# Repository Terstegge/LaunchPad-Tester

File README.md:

# LaunchPad-Tester
This is a small TI-LaunchPad compatible boosterpack board,
which can be used for testing all GPIO pins on a TI LaunchPad.

_Background:_ When using TI LaunchPads for educational purposes,
some of the IO-pins might be destroyed by students. So I needed
a simple way to test all IO pins of such boards before using
the boards during the next semester.

I had some spare [CY8C9540A](http://www.cypress.com/file/37971/download)
chips from Cypress and some 5mm 3-color LEDS, which are now used on
this board. The CY8C9540A is a GPIO expander with 40 IO pins and a
(slow) I2C interface. It also supports a programmable PWM signal on
all pins. Two of the LaunchPad IO pins are used for the I2C interface
to operate the CY8C9540A. When the CY8C9540A is not detected by the
LaunchPad, we at least know that these two pins are not working :).

When the CY8C9540A is detected by software, we can test every single
LaunchPad pin in input- and output-mode by programming the connected
CY8C9540A-pin.

The 3-color LED can be used to show the results of the tests.

This project contains the hardware design files, which were developed
using [KiCad EDA](http://kicad.org/). The related software will be
published in a separate project.

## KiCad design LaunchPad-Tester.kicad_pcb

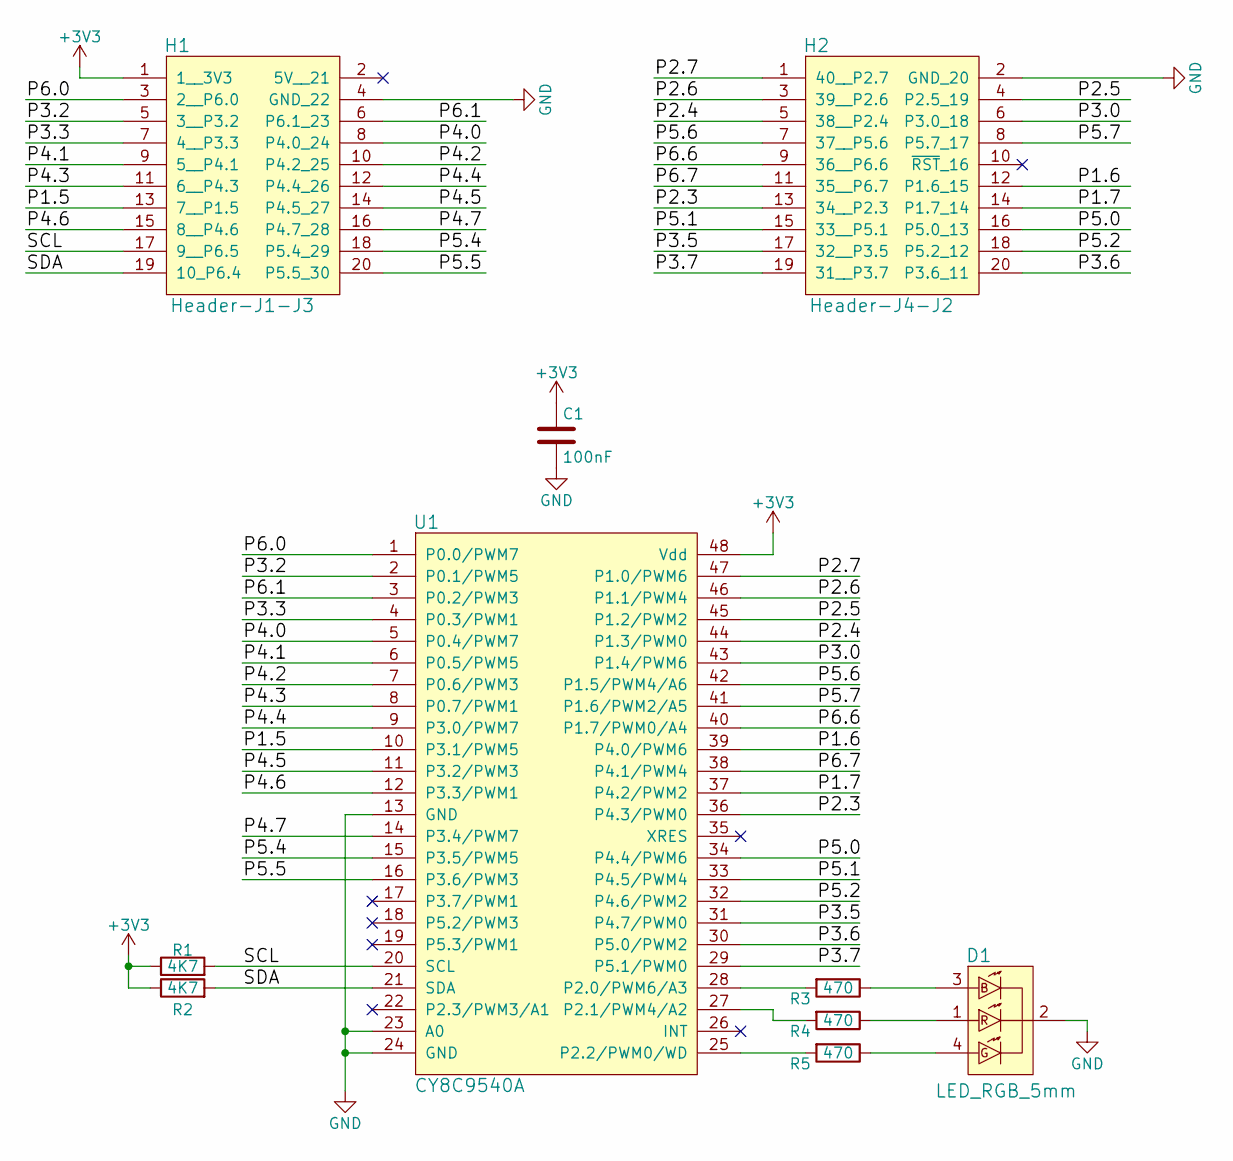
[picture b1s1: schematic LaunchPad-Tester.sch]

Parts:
C1: 100nF; C_0805
D1: LED_RGB_5mm; LED_D5.0mm-4
H1: Header-J1-J3; Socket_Strip_Straight_2x10_Pitch2.54mm
H2: Header-J4-J2; Socket_Strip_Straight_2x10_Pitch2.54mm
R1, R2: 4K7; R_0805
R3, R4, R5: 470; R_0805
U1: CY8C9540A; SSOP-48_7.5x15.9mm_Pitch0.635mm

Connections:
+3V3: C1.1, H1.1 (1__3V3), R1.1, R2.1, U1.48 (Vdd)
/P1.5: H1.13 (7__P1.5), U1.10 (P3.1/PWM5)
/P1.6: H2.12 (P1.6_15), U1.39 (P4.0/PWM6)
/P1.7: H2.14 (P1.7_14), U1.37 (P4.2/PWM2)
/P2.3: H2.13 (34__P2.3), U1.36 (P4.3/PWM0)
/P2.4: H2.5 (38__P2.4), U1.44 (P1.3/PWM0)
/P2.5: H2.4 (P2.5_19), U1.45 (P1.2/PWM2)
/P2.6: H2.3 (39__P2.6), U1.46 (P1.1/PWM4)
/P2.7: H2.1 (40__P2.7), U1.47 (P1.0/PWM6)
/P3.0: H2.6 (P3.0_18), U1.43 (P1.4/PWM6)
/P3.2: H1.5 (3__P3.2), U1.2 (P0.1/PWM5)
/P3.3: H1.7 (4__P3.3), U1.4 (P0.3/PWM1)
/P3.5: H2.17 (32__P3.5), U1.31 (P4.7/PWM0)
/P3.6: H2.20 (P3.6_11), U1.30 (P5.0/PWM2)
/P3.7: H2.19 (31__P3.7), U1.29 (P5.1/PWM0)
/P4.0: H1.8 (P4.0_24), U1.5 (P0.4/PWM7)
/P4.1: H1.9 (5__P4.1), U1.6 (P0.5/PWM5)
/P4.2: H1.10 (P4.2_25), U1.7 (P0.6/PWM3)
/P4.3: H1.11 (6__P4.3), U1.8 (P0.7/PWM1)
/P4.4: H1.12 (P4.4_26), U1.9 (P3.0/PWM7)
/P4.5: H1.14 (P4.5_27), U1.11 (P3.2/PWM3)
/P4.6: H1.15 (8__P4.6), U1.12 (P3.3/PWM1)
/P4.7: H1.16 (P4.7_28), U1.14 (P3.4/PWM7)
/P5.0: H2.16 (P5.0_13), U1.34 (P4.4/PWM6)
/P5.1: H2.15 (33__P5.1), U1.33 (P4.5/PWM4)
/P5.2: H2.18 (P5.2_12), U1.32 (P4.6/PWM2)
/P5.4: H1.18 (P5.4_29), U1.15 (P3.5/PWM5)
/P5.5: H1.20 (P5.5_30), U1.16 (P3.6/PWM3)
/P5.6: H2.7 (37__P5.6), U1.42 (P1.5/PWM4/A6)
/P5.7: H2.8 (P5.7_17), U1.41 (P1.6/PWM2/A5)
/P6.0: H1.3 (2__P6.0), U1.1 (P0.0/PWM7)
/P6.1: H1.6 (P6.1_23), U1.3 (P0.2/PWM3)
/P6.6: H2.9 (36__P6.6), U1.40 (P1.7/PWM0/A4)
/P6.7: H2.11 (35__P6.7), U1.38 (P4.1/PWM4)
/SCL: H1.17 (9__P6.5), R1.2, U1.20 (SCL)
/SDA: H1.19 (10_P6.4), R2.2, U1.21 (SDA)
GND: C1.2, D1.2, H1.4 (GND_22), H2.2 (GND_20), U1.13 (GND), U1.23 (A0), U1.24 (GND)
unnamed: D1.1, R4.1
unnamed: D1.3, R3.1
unnamed: D1.4, R5.1
unnamed: R3.2, U1.28 (P2.0/PWM6/A3)
unnamed: R4.2, U1.27 (P2.1/PWM4/A2)
unnamed: R5.2, U1.25 (P2.2/PWM0/WD)

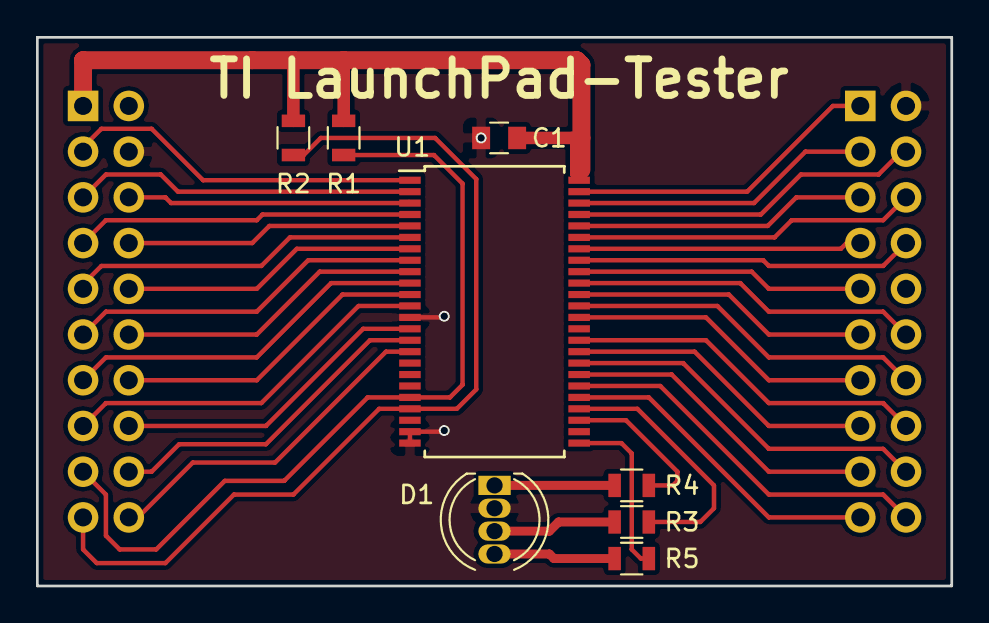
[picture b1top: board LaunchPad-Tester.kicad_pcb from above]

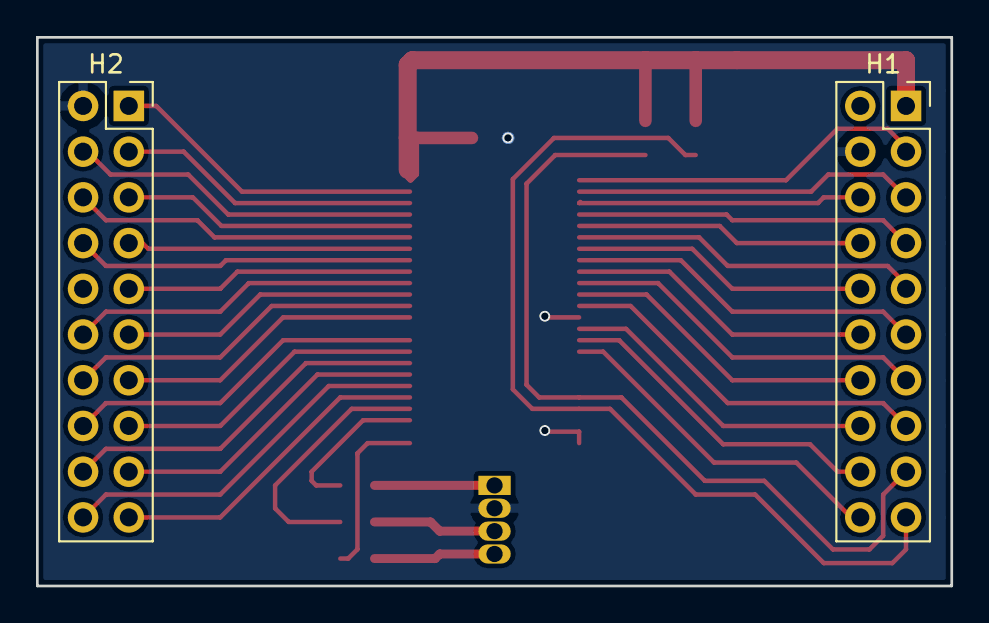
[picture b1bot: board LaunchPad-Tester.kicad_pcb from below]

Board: 2 copper layers, 50.8 x 30.5 mm, 10 parts (2 on the bottom side), 43 nets.

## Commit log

2017-08-24 First version of Launchpad Tester. Maybe also the last version ;)
2017-08-24 Added picture of board.
2017-08-24 Added README.
2017-08-24 Update README.md
    Small typos corrected.
2017-08-24 Update README.md
    One more typo ...
2017-08-24 Added schematics as PDF file.
2017-09-08 Renamed project to LaunchPad-Tester and coorected some typos.
2017-09-08 Updated picture with new project name.
2021-11-10 Update README.md
    https://forum.kicad.info/t/warning-avoid-all-links-to-kicad-pcb-org-use-kicad-org/31521
2021-11-12 Updated link to KiCad.
